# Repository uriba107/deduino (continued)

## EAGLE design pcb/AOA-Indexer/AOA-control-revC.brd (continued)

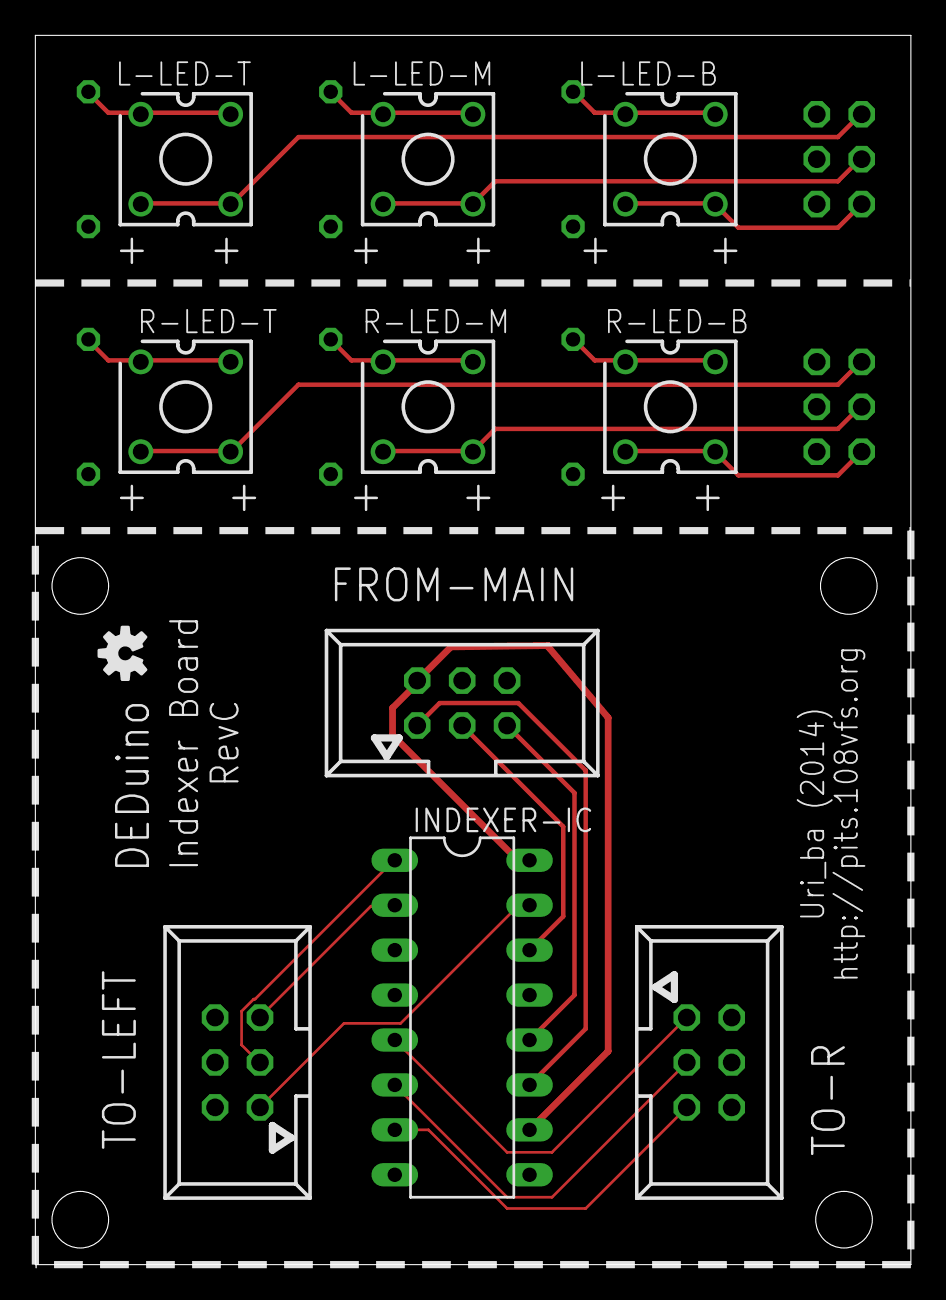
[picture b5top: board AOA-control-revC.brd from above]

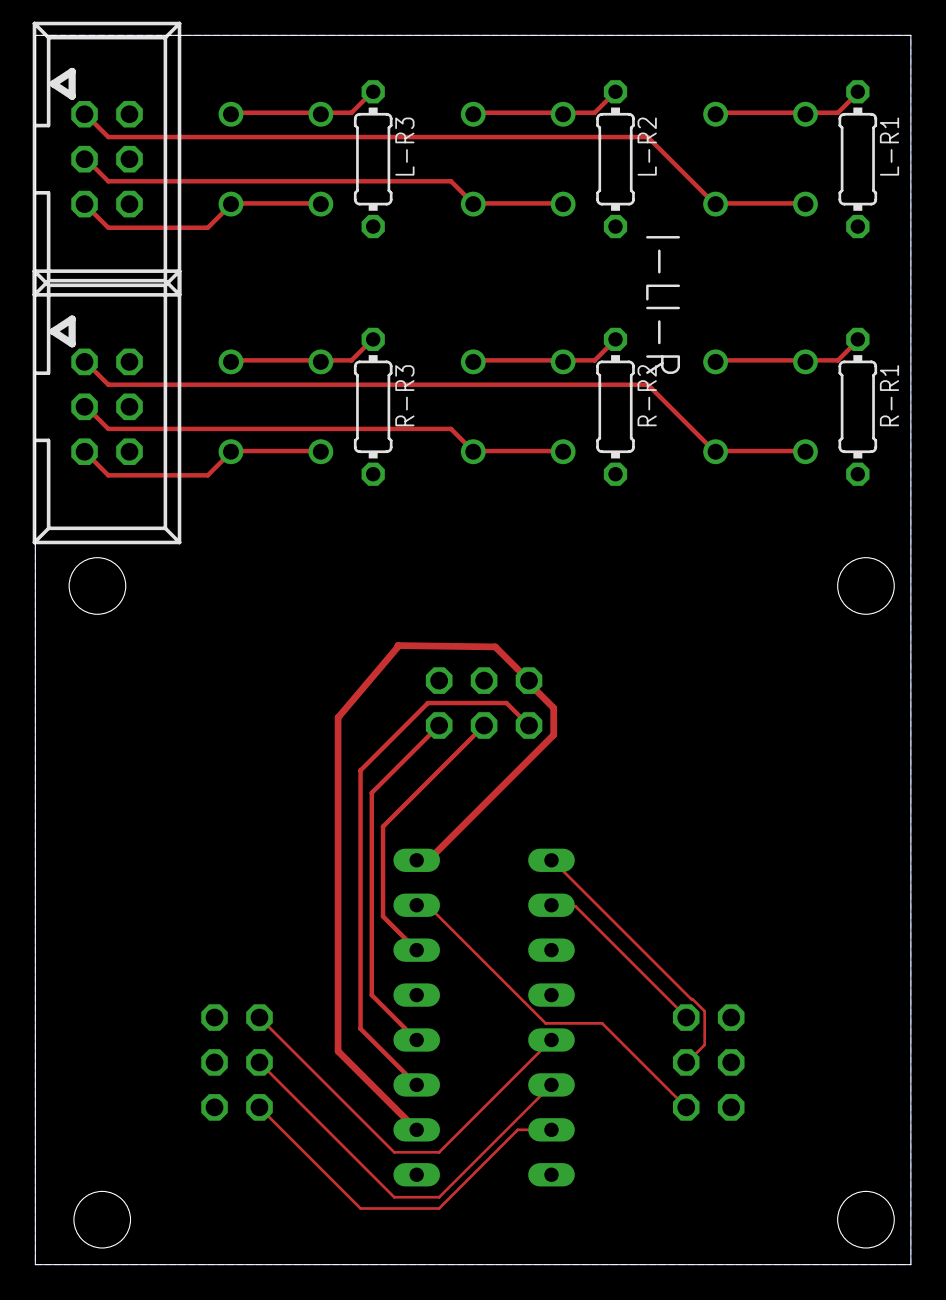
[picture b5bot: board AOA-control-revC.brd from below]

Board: 2 copper layers, 49.5 x 69.5 mm, 19 parts (8 on the bottom side), 23 nets.

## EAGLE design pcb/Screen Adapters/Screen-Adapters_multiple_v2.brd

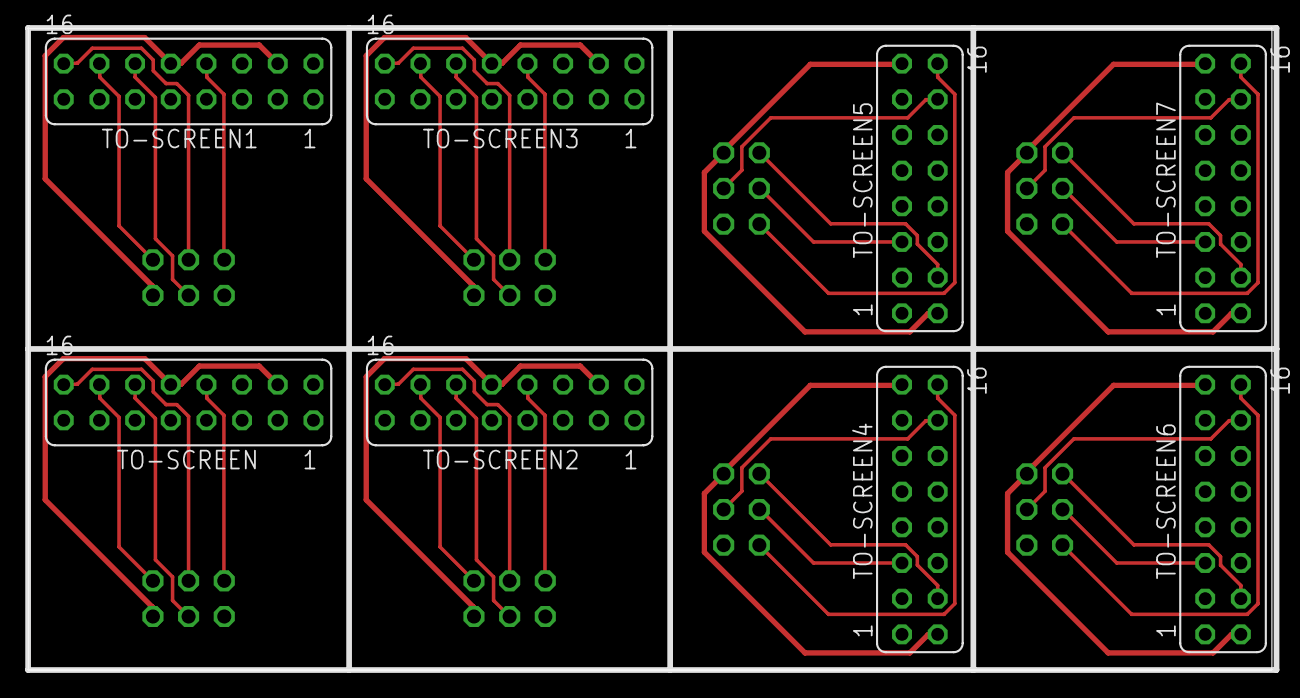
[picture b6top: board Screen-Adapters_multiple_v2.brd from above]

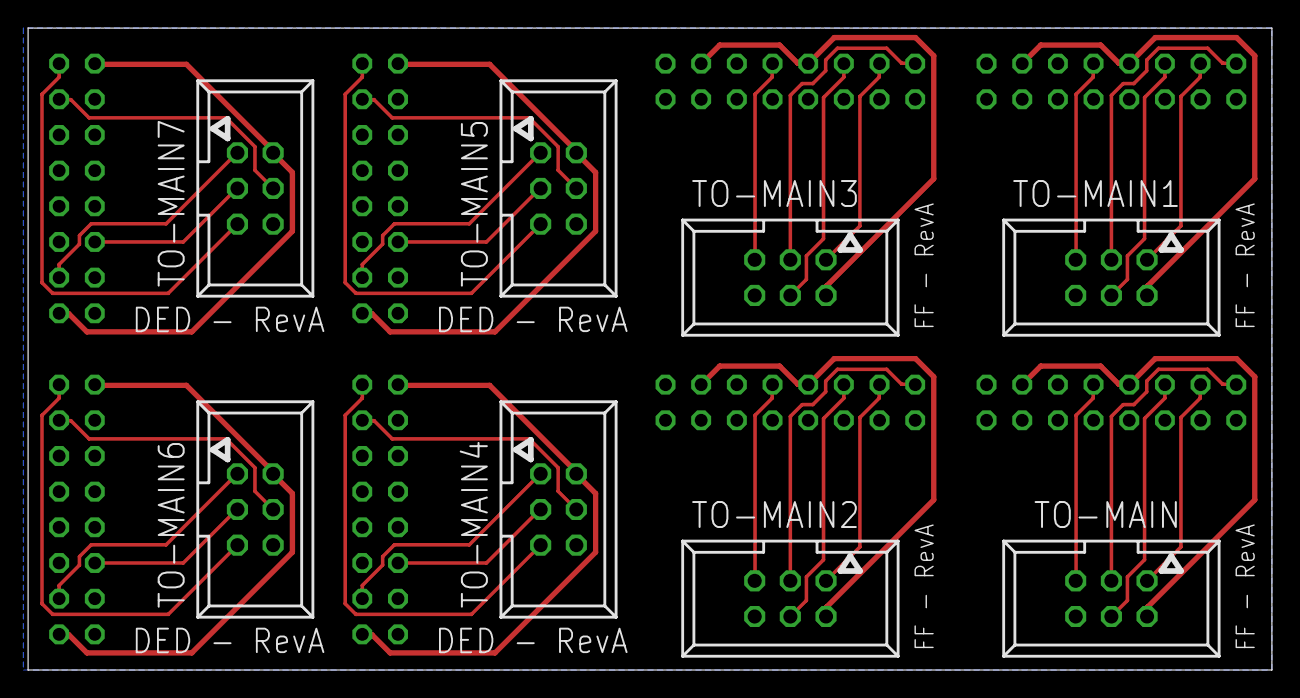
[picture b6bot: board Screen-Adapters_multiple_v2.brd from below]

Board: 2 copper layers, 88.6 x 45.7 mm, 16 parts (8 on the bottom side), 41 nets.

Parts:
TO-MAIN, TO-MAIN1, TO-MAIN2, TO-MAIN3, TO-MAIN4, TO-MAIN5, TO-MAIN6, TO-MAIN7: 057-006-1
TO-SCREEN, TO-SCREEN1, TO-SCREEN2, TO-SCREEN3, TO-SCREEN4, TO-SCREEN5, TO-SCREEN6, TO-SCREEN7: FE08-2

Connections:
5V: TO-MAIN.2, TO-SCREEN.4, TO-SCREEN.10
5V1: TO-MAIN1.2, TO-SCREEN1.4, TO-SCREEN1.10
5V2: TO-MAIN2.2, TO-SCREEN2.4, TO-SCREEN2.10
5V3: TO-MAIN3.2, TO-SCREEN3.4, TO-SCREEN3.10
5V4: TO-MAIN4.2, TO-SCREEN4.2, TO-SCREEN4.15
5V5: TO-MAIN5.2, TO-SCREEN5.2, TO-SCREEN5.15
5V6: TO-MAIN6.2, TO-SCREEN6.2, TO-SCREEN6.15
5V7: TO-MAIN7.2, TO-SCREEN7.2, TO-SCREEN7.15
CLK: TO-MAIN.1, TO-SCREEN.14
CLK1: TO-MAIN1.1, TO-SCREEN1.14
CLK2: TO-MAIN2.1, TO-SCREEN2.14
CLK3: TO-MAIN3.1, TO-SCREEN3.14
CLK4: TO-MAIN4.1, TO-SCREEN4.4
CLK5: TO-MAIN5.1, TO-SCREEN5.4
CLK6: TO-MAIN6.1, TO-SCREEN6.4
CLK7: TO-MAIN7.1, TO-SCREEN7.4
DISP_A0: TO-MAIN.4, TO-SCREEN.12
DISP_A1: TO-MAIN1.4, TO-SCREEN1.12
DISP_A2: TO-MAIN2.4, TO-SCREEN2.12
DISP_A3: TO-MAIN3.4, TO-SCREEN3.12
DISP_A4: TO-MAIN4.4, TO-SCREEN4.14
DISP_A5: TO-MAIN5.4, TO-SCREEN5.14
DISP_A6: TO-MAIN6.4, TO-SCREEN6.14
DISP_A7: TO-MAIN7.4, TO-SCREEN7.14
GND: TO-MAIN.6, TO-MAIN1.6, TO-MAIN2.6, TO-MAIN3.6, TO-MAIN4.6, TO-MAIN5.6, TO-MAIN6.6, TO-MAIN7.6, TO-SCREEN.2, TO-SCREEN1.2, TO-SCREEN2.2, TO-SCREEN3.2, TO-SCREEN4.1, TO-SCREEN4.7, TO-SCREEN4.8, TO-SCREEN4.9, TO-SCREEN4.10, TO-SCREEN4.11, TO-SCREEN4.12, TO-SCREEN4.13, TO-SCREEN5.1, TO-SCREEN5.7, TO-SCREEN5.8, TO-SCREEN5.9, TO-SCREEN5.10, TO-SCREEN5.11, TO-SCREEN5.12, TO-SCREEN5.13, TO-SCREEN6.1, TO-SCREEN6.7, TO-SCREEN6.8, TO-SCREEN6.9, TO-SCREEN6.10, TO-SCREEN6.11, TO-SCREEN6.12, TO-SCREEN6.13, TO-SCREEN7.1, TO-SCREEN7.7, TO-SCREEN7.8, TO-SCREEN7.9, TO-SCREEN7.10, TO-SCREEN7.11, TO-SCREEN7.12, TO-SCREEN7.13
MOSI: TO-MAIN.3, TO-SCREEN.16
MOSI1: TO-MAIN1.3, TO-SCREEN1.16
MOSI2: TO-MAIN2.3, TO-SCREEN2.16
MOSI3: TO-MAIN3.3, TO-SCREEN3.16
MOSI4: TO-MAIN4.3, TO-SCREEN4.5
MOSI5: TO-MAIN5.3, TO-SCREEN5.5
MOSI6: TO-MAIN6.3, TO-SCREEN6.5
MOSI7: TO-MAIN7.3, TO-SCREEN7.5
SELECT: TO-MAIN.5, TO-SCREEN.8
SELECT1: TO-MAIN1.5, TO-SCREEN1.8
SELECT2: TO-MAIN2.5, TO-SCREEN2.8
SELECT3: TO-MAIN3.5, TO-SCREEN3.8
SELECT4: TO-MAIN4.5, TO-SCREEN4.16
SELECT5: TO-MAIN5.5, TO-SCREEN5.16
SELECT6: TO-MAIN6.5, TO-SCREEN6.16
SELECT7: TO-MAIN7.5, TO-SCREEN7.16

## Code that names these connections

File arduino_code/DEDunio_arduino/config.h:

///////////////////////////////////////////////////////////////////////
// Select Arduino Type - Uncomment correct board type                //
///////////////////////////////////////////////////////////////////////

//// Arduino Uno is the default as it is the most common - how ever it is NOT the recommended Arduino to use due to it's low amount of SRAM
//// Arduino Micro is considered the Minimum at this stage of the project
//// Arduino Due is the recommended Arduino in the long run (able to support future expansions)
//// There are two USB connections on the DUE, the NATIVE is the recommended, but in some cases driver issues may strike.

//#define ARDUINO_UNO
//#define ARDUINO_MICRO
//#define ARDUINO_PRO_MICRO
//#define ARDUINO_DUE_NATIVE
#define ARDUINO_DUE_PROG



///////////////////////////////////////////////////////////////////////
// Module Defines                                                    //
// Uncomment The modules you want                                    //
// Without this settings Nothing will work                           //
// NOTE: Lights are going to be overhauled in V1.2                   //
///////////////////////////////////////////////////////////////////////

#define Screens //global enable screens
#define Lights //global enable lights 


///////////////////////////////////////////////////////////////////////
// Sub-Module Defines                                                //
// Uncomment The modules you want                                    //
///////////////////////////////////////////////////////////////////////
#ifdef Screens
  #define DED_on
  #define FuelFlow_on
//  #define PFD_on 
//  #define CMDS_on 
//  #define SpeedBreaks_on
#endif

#ifdef Lights
// Select transfer protocol (SPI or I2C)
// SPI is retained for legacy support I2C is preferable
  //#define USE_SPI
  #define USE_I2C
  
// Choose what to light up
// Available to both protocols
  #define Indexers_on
//  #define CautionPanel_on 

// Available only on I2C
//  #define Glareshield_on 
#endif


///////////////////////////////////////////////////////////////////////
// Sub-Module config                                                 //
// Uncomment The options you want to enable                          //
///////////////////////////////////////////////////////////////////////


////////// DED/PFL //////////
// uncomment to rotate display 180Degrees
//#define rotateDED
//#define rotatePFD

////////// FFI //////////
//*****************************************************************************************//
//** NOTE:                                                                               **// 
//** Due to performance issues, when using Arduino Uno,                                  **//
//** The RealFFI animation and the Bezel will be Automaticly disabled (check fuelflow.h) **//
//*****************************************************************************************//

//// Select the correct FFI display driver
//// SSD1306 dispaly drivers (such as the ones sold by Adafruit and sparkfun)
#define FFI_SSD1306

//// SH1106 display drivers (commonly found on ebay)
//#define FFI_SH1106

//** NOTE: Ebay bought displays are sometime mislabled and SH1106 displays may be SSD1306 (and vice versa) **//

/// Define bezel to draw FUEL FLOW and PPH on screen.
//// Bezel reduces FPS considerably - if you build a real Bezel, this option should be off
#define Bezel

//// Define RealFFI to draw "Real" FFI - when not defined a BMS style FFI is drawn
//// Real FFI animation requires more RAM available there for is not suitable for an Uno if DED/PFL are enabled
//// This feature will be automaticly disabled when using arduino Uno
#define RealFFI

////////// SpeedBreaks //////////
//// Select the correct SB display driver
//// SSD1306 dispaly drivers (such as the ones sold by Adafruit and sparkfun)
#define SB_SSD1306

//// SH1106 display drivers (commonly found on ebay)
//#define SB_SH1106


////////// DEBUGGING //////////
//// Enable crosshair to help align text on screens ////
//#define crosshair

///*************** DO NOT EDIT BELOW THIS LINE WITHOUT INTENT! ***************//
// if any of the DUE options are enabled, enable the global DUE flag
#if defined(ARDUINO_DUE_NATIVE) || defined(ARDUINO_DUE_PROG)
  #define ARDUINO_DUE
#endif
///////////////////////////////////////////////////////////////////////
// Sub-Module Pinout configurations                                  //
// (Advanced settings - Don't change unless you mean it              //
///////////////////////////////////////////////////////////////////////

// Screen pins should be relativly static
#ifdef Screens
  #if defined(ARDUINO_UNO) || defined(ARDUINO_DUE)
    #define DISP_A0 9
    #define DED_SEL 8
    #define FF_SEL 7
    #define PFD_SEL 6
    #define CMDS_SEL 5
    #define EXT1_SEL 4
    #define EXT2_SEL 3
  #endif

  #ifdef ARDUINO_MICRO
    #define DISP_A0 12
    #define DED_SEL 11
    #define FF_SEL 10
    #define PFD_SEL 9
    #define CMDS_SEL 8
    #define EXT1_SEL 7
    #define EXT2_SEL 6
  #endif
  
  #ifdef ARDUINO_PRO_MICRO
    #define DISP_A0 10
    #define DED_SEL 9
    #define FF_SEL 8
    #define PFD_SEL 7
    #define CMDS_SEL 6
    #define EXT1_SEL 5
    #define EXT2_SEL 4
  #endif
  
#endif

// Adjust i2c addresses to fit your rig.
// you will probably need to adjust the lights_i2c.h and i2c_hardware.h to suit your specific board/hardware
#ifdef Lights
   #ifdef USE_I2C
       #define AoaAddr 0x20
       #define CpAddr  0x21
//       #define CpAddr2  0x22
       #define GsAddr  0x23

   #endif
// Retained for Legacy support - i2c is preferable.
   #ifdef USE_SPI
       #define AoaLatchPin 2 // AOA indexed
       #define CpLatchPin 3 // Caution Panels
   #endif
#endif

////////// INTERNAL VARS //////////
// How many seconds should go by before screens turn off after no response recived to the "I'm alive" signal
#define SLEEP_TIMER 120000 // 120 seconds In Miliseconds

// How many milliseconds go before the displays reset after initillizing (for user inspection)
#define POST_BOOT_BIT 4000

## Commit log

2014-11-06 fixed read me
2014-11-08 Another fix on readme
2014-11-12 Added address for blog
2014-11-29 Preparing V1.1
    Added new DED font by "cool hand"
    Added new new FFi font by "Moon"
    Added drawn FFi bezel - concept by "Topper Harly"
    Updated connector app to v0.0.0.2 - which solves some issues with DED
    chars being cropped
    :
2014-11-29 PFD now uses new font as well by default. Adjusted horizontal offset for DED adn PFD. Reverted to Uno as default device
2014-12-03 Version 1.1.1 - initial commit New Fuelflow font - based on the Real MilSpec 33558 font. Thank you "Moon" and "AiRdAncE" for references, links and help. drawn Bezel is enabled by default - font is th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
    PFD now uses new font as well by default. Adjusted horizontal offset for DED adn PFD. Reverted to Uno as default device
2014-12-06 Another itteration for the FFI font and code - Thanks AiRdAncE
2014-12-06 initial commit for v1.1.3 New mode called "RealFFI" - which animates the top two digits as well, blocking boxes are only drawn with the "Bezel" feature on to reduce FPS hit if using a real front plat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
    TODO: create a blank character for the FFtt (No 0 or 9) - adjust logic accordingly
2014-12-07 V1.1.3
    More improvemnts on FFI
    New FFI animation mode:
    "BMS" - FFI is rendered as the BMS one. animated Hundreds, the rest are jumping
    "RealFFI" - FFI is rendered as the Real thing, no 0 on higher numbers, rollover on all three top digits. (lower FPS)
    both modes include an optional Bezel drawn on top of the screen.
    font is set to be at the correct size with the Bezel off. Bezel on reduces the "window" size compared to the real FFI.
2014-12-09 consolidate every user controlled option to config.h
2014-12-09 Fix FFI not rolling properly with DED disabled. Advanced version on ino file
2014-12-20 initial commit to refractured code
2014-12-20 config.h refracting
    All important configuration options are now located on "config.h" file - no need to fuss around in the code
    Arduino Micro is now the default controller. Arduino Uno still works, but Bezel and RealFFI are autocratically disabled on it for performance reasons.
    Hopefully this will be the last of the SPI based light system releases. so please be aware when designing boards. - current AOA and Caution panel will still be available via SPI as they are now.
2014-12-20 Updated date and version
2015-01-25 Fix for Arduino Due not allowing FFi to work properly. updated included u8glib to v1.17
2015-02-09 small Endianess fix for Due, another tweak to sort out the FFI bug
2015-02-10 app upgraded to 0.0.0.3
2015-02-19 fixes for Main board design, added pdf schematic for the screen adapter
2015-02-19 initial commit for the 1.2 version - adding i2c support for lights
2015-03-29 1.2.0-alpha2 Display timeout and some bugfixes
2015-03-29 Moon's DED font is now default. Extended the "GoDark" timeout to 120 seconds.
2015-04-02 DEDuino.exe - now version 0.0.0.4 Removed F4SharedMem.dll as it is now merged into the exe.
2015-04-02 new PCB layouts
2015-04-05 App version 0.0.0.5 Bugfix for minimize to systray If autolaunch, will launch minimized.
2015-07-22 1.2.0-alpha3 u8glib updated to last version Fixed flicker and stutter issues on Due Adjusted for Arduino IDE 1.6.5
2015-07-22 Connector App updated to v0.0.6 Fixes to minimize logic
2015-07-24 1.2.0-alpha4 Bug fixes Initial very raw implementation of CMDS - still need to tune font,position and data transfer. (strictly experimental)
2015-07-30 Version 1.2.0-alpha5 requires app version 0.0.0.8 Streamlined the communication protocol. better performance and better data consistency. new "lights out" protocol.
2015-07-30 App version 0.0.0.8
2015-07-30 App 0.0.0.8b bugfix for uninitialized variable on first falcon launch.
2015-08-07 0.0.0.8c - fixed CTD
2015-08-07 1.2.0-alpha5b
2015-08-07 App version 0.0.0.9
2015-08-07 1.2.0-alpha6 initial support for Glareshield lights
2015-08-12 1.2.0-alpha7 Added option to use Due Programming port
2015-08-12 App version 0.0.0.11 in support of 1.2.0-alpha7
2015-08-12 Added FF adapter schematic in PDF format
2015-08-13 Fix functions to support Jshep's CP
2015-08-13 App v0.0.0.11b - Small bugfixes on Jshep CP mode
2015-08-14 Adjustments to support JShep's Caution panel.
2015-08-14 Disabled Moon's DED font due to a bug that I missed. it will be re-enabled once Font is fixed CoolHand's original Widefont is the default
2015-08-14 App Version 0.0.1.0 New DLL. re-factoring intended to make adding light bits easier. enough progress to earn the 0.0.1 milestone
2015-08-16 Updated Moon's Widefont to fix char order error. tweaked spacing and re-enabled moon's as default.
2015-08-16 1.2.0-alpha8 Glareshield no longer experimental and will be included in 1.2.0 TODO: Reference schematic.
2015-08-18 1.2.0-Beta1
2015-08-18 added eyebrow circuit reference
2015-08-18 Caution panel - rename
2015-08-18 removed an un-needed "0"
2015-08-21 V1.2.0
2015-08-22 initial SB support TODO: improve barber pole and better AA on font
2015-08-23 Speedbreaks tuning, better image and animation
2015-08-26 App v0.0.1.1
2015-08-26 Initial support for "Pro Micro"
2015-09-14 Fix falcon Version checkbox
2015-09-14 Initial Support in Adruino Pro-micro
2015-10-17 New version - now checks COM exists before connecting
2017-01-23 1.3.0-Alpha1 * migration from u8glib to u8g2
2017-01-23 Updated readme and added missing files
2017-01-23 Removing Un-used u8lib fonts
